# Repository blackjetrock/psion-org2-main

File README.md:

# Psion Organiser 2 Recreation Main PCB

A recreation of the Psion Organiser II main PCB using a RP Pico as the
main processor.
An OLED display replaces the original LCD, datapack gadgets supply the
non volatile storage using SD cards.
A ESP-WROOM-32 module on the board provides Wifi and maybe Bluetooth connectivity.
The module provides a hot spot that can be used to perfom actions on the Organiser
and transfer data.

The code running will hopefully be an emulation of the 6303 running one of the original
organiser ROMs with the hardware emulation done on the Pico.

Main PCB
========

This has a RP Pico on it as a controller and several IO expanders. These are because the Pico doesn't have enough GPIOs to
run all of the hardware that is needed.

Power PCB
=========

The original power PCB doesn't really fit with the new main board, so rather than try to work around it, A new PCB is used with the
new main board. It has the slot connectors and any hardware needed to drive them. The slot level shifters are on this board. It would be possible to design a different poiwer PCB that, for example, didn't have slots but had sd cards instead. The hardware for the slots is then replaced by the new PCB, but the main PCB still has whatever circuitry is needed for its own hardware.

Emulator
========

It's a bit of an odd place for it, but there is an emulator here that I used as the basis for the emulator that runs on the recreation. I did the bulk of the work on it on a PC and then moved i tto the Pico. There's now separate code for the Pico as it supports hardware on the main PCB rather than PC based keyboard and display IO. The mon-emulator is a monitored emulator that uses a second emulator to check the operation of mine so that I could find some tricky bugs. The emulator that does the monitoring is the 6303 file from Jaap's Jape emulator, ported to C.

Display
=======

The display is an OLED dot matrix graphics display. I have tried several colours, they all work, the white display is clearest I think.

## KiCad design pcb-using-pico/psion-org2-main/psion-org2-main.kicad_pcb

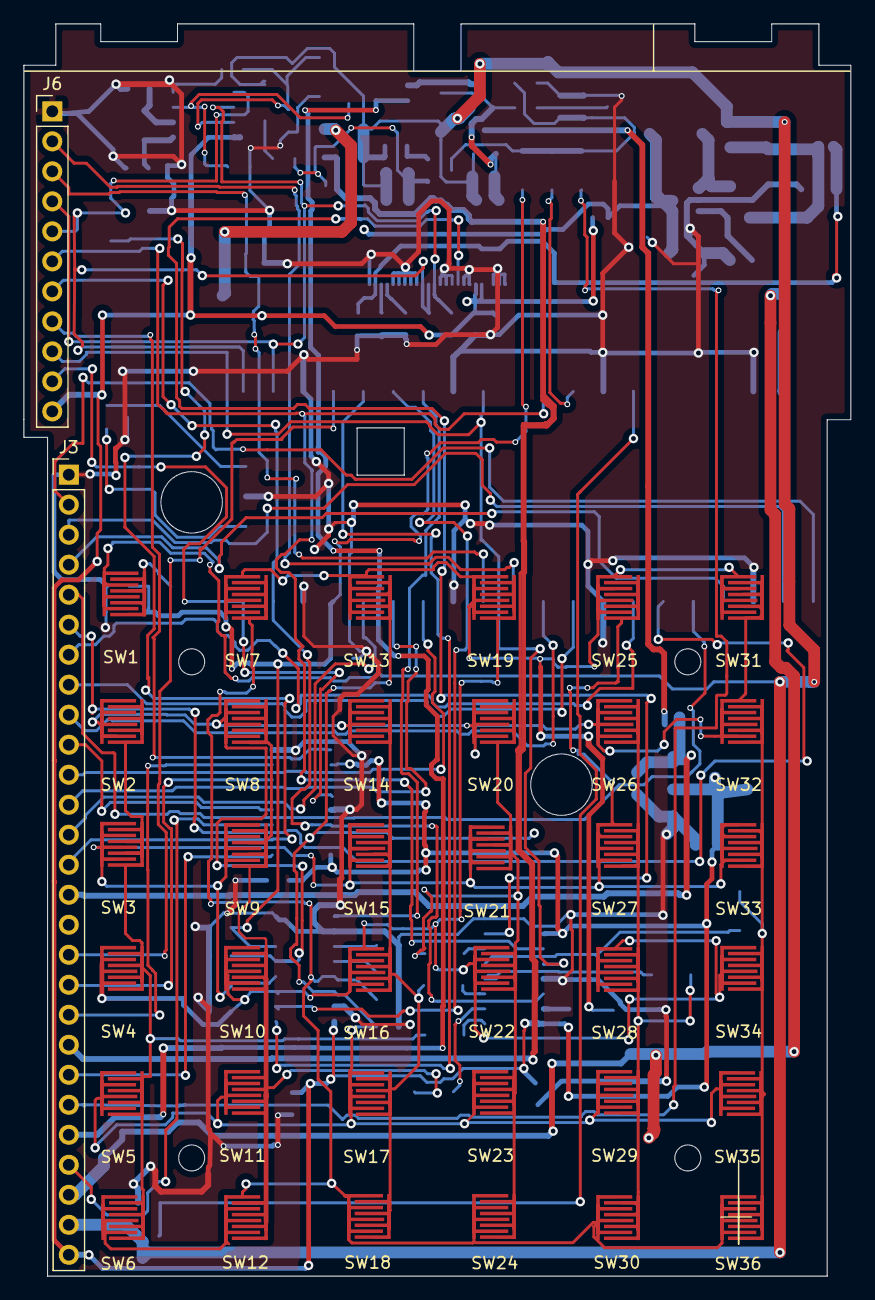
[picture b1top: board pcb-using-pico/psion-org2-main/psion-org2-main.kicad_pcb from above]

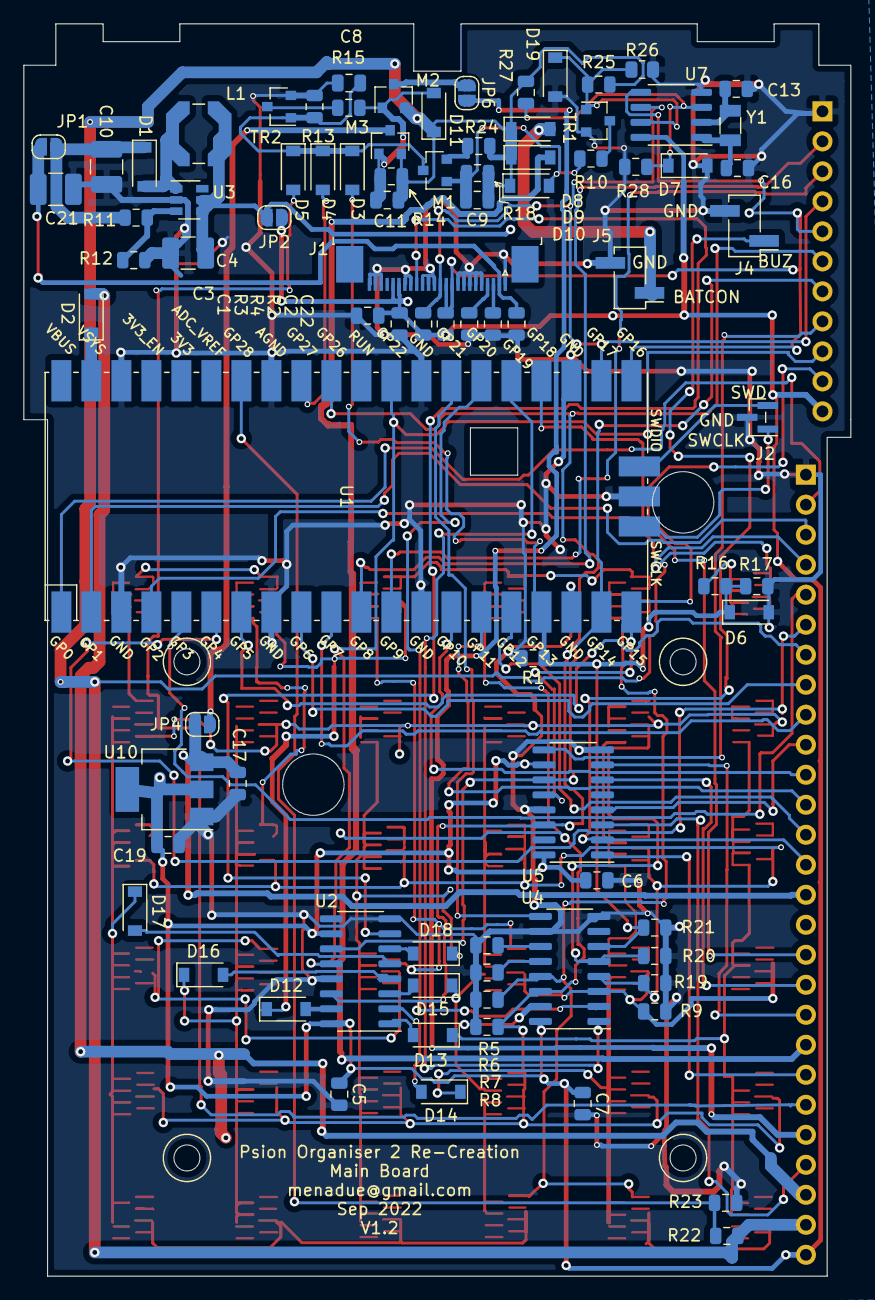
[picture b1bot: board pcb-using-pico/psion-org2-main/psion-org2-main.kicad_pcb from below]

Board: 2 copper layers, 70.0 x 106.0 mm, 124 parts (86 on the bottom side), 87 nets.

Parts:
C1: 4u7; C_0805_2012Metric
C2: 4u7 25V; C_0805_2012Metric
C3, C5, C6, C7, C8, C9, C11, C22: 100nF; C_0805_2012Metric
C4, C10: 22uF; C_1210_3225Metric_Pad1.42x2.65mm_HandSolder
C13, C16: 10pF; C_0805_2012Metric
C17, C19: 100n; C_0805_2012Metric
C21: 10uF; C_1210_3225Metric_Pad1.42x2.65mm_HandSolder
D1: SS36; D_SOD-123
D2: MBR120VLSFT1G; D_SOD-123
D3, D4, D5, D12, D13, D14, D15, D16, D17, D18: 1N4148; D_SOD-123
D6: 2v7; D_SOD-123
D7, D19: nopop; D_SOD-123
D8, D9: AECQ101; D_SOD-123
D10, D11: 4v7; D_SOD-123
J1: Conn_01x24_Female; TE_2-1734839-4_1x24-1MP_P0.5mm_Horizontal_reversed_pinout
J2: Conn_01x03_Female; PinHeader_1x03_P1.00mm_Vertical_SMD_Pin1Left
J3: Conn_01x27_Female; PinHeader_1x27_P2.54mm_Vertical
J4, J5: Conn_01x02_Female; PinHeader_1x02_P2.54mm_Vertical_SMD_Pin1Left
J6: Conn_01x11_Female; PinHeader_1x11_P2.54mm_Vertical
JP1: SolderJumper_2_Open; SolderJumper-2_P1.3mm_Open_RoundedPad1.0x1.5mm
JP2, JP4, JP6: Jumper_NO_Small; SolderJumper-2_P1.3mm_Open_RoundedPad1.0x1.5mm
L1: 22uH; L_Coilcraft_LPS5030
M1, M2, M3: Si2301; SOT-23
R1, R10, R13, R14, R15, R18, R24, R25, R26: 10k; R_0805_2012Metric
R2: 910k; R_0805_2012Metric
R3, R4: 2k; R_0805_2012Metric
R5, R6, R7, R8, R9, R19, R20, R21: 100k; R_0805_2012Metric
R11, R27: 110k; R_0805_2012Metric
R12: 5789R; R_0805_2012Metric
R16: 2k2; R_0805_2012Metric
R17: nopop; R_0805_2012Metric
R22: Not tested or calculated yet; R_0805_2012Metric
R23: Not tested of calculated yet; R_0805_2012Metric
R28: 47k; R_0805_2012Metric
SW1: AC_ON; fx502p_keypad
SW2: A; fx502p_keypad
SW3: g; fx502p_keypad
SW4: m; fx502p_keypad
SW5: s; fx502p_keypad
SW6: shft; fx502p_keypad
SW7: mode; fx502p_keypad
SW8: b; fx502p_keypad
SW9: h; fx502p_keypad
SW10: n; fx502p_keypad
SW11: t; fx502p_keypad
SW12: del; fx502p_keypad
SW13: up; fx502p_keypad
SW14: c; fx502p_keypad
SW15: i; fx502p_keypad
SW16: o; fx502p_keypad
SW17: u; fx502p_keypad
SW18: y; fx502p_keypad
SW19: down; fx502p_keypad
SW20: d; fx502p_keypad
SW21: j; fx502p_keypad
SW22: p; fx502p_keypad
SW23: v; fx502p_keypad
SW24: z; fx502p_keypad
SW25: left; fx502p_keypad
SW26: e; fx502p_keypad
SW27: k; fx502p_keypad
SW28: q; fx502p_keypad
SW29: w; fx502p_keypad
SW30: spc; fx502p_keypad
SW31: right; fx502p_keypad
SW32: f; fx502p_keypad
SW33: L; fx502p_keypad
SW34: r; fx502p_keypad
SW35: x; fx502p_keypad
SW36: exe; fx502p_keypad
TR1: Si2302CDS-n-ch; SOT-23
TR2: Si2302CDS-n-channel; SOT-23
U1: Pico; RPi_Pico_SMD
U2, U5: 74HC595; SOIC-16_3.9x9.9mm_P1.27mm
U3: Regulator_Switching_MT3608; SOT-23-6
U4: 74LS165; SOIC-16_3.9x9.9mm_P1.27mm
U7: MCP7940N-xSN; SO-8_3.9x4.9mm_P1.27mm
U10: AMS1117-3.3; SOT-223-3_TabPin2
Y1: 32k768Hz; Crystal_SMD_3215-2Pin_3.2x1.5mm

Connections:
5V: D2.2, J3.25
5V_ON: J3.24, U5.3
+3V3: C1.1, C3.1, C5.1, C6.1, C7.1, C19.1, J1.5, J1.6, J3.27, J6.11, JP2.1, R3.1, R4.1, U2.10, U2.16, U4.16, U5.10, U5.16, U7.8, U10.2
BATCON: D8.2, J5.1
BUZZER: J3.14, J4.1, U5.2
ESP_ON: J3.21, U5.1
EXT_PWR_IN: D9.2, J3.20
EX_ON: D5.2, J3.22
GND: C1.2, C2.2, C3.2, C4.2, C5.2, C6.2, C7.2, C8.2, C10.2, C13.2, C16.2, C17.2, C19.2, C21.2, C22.2, D6.2, D7.2, D19.2, J1.1, J1.2, J1.3, J1.7, J1.8, J1.10, J1.11, J1.12, J1.16, J1.17, J1.18, J1.19, J1.20, J1.24, J2.2, J3.1, J4.2, J5.2, J6.1, R1.2, R2.2, R5.2, R6.2, R7.2, R8.2, R9.2, R12.2, R13.2, R17.2, R19.2, R20.2, R21.2, R23.2, R26.2, R28.2, TR1.2, TR2.2, U1.3, U1.8, U1.13, U1.18, U1.23, U1.28, U1.33, U1.38, U1.42, U2.8, U2.13, U3.2, U4.8, U4.10, U4.15, U5.8, U5.13, U7.4, U10.1
K1: D12.1, SW7.1, SW13.1, SW19.1, SW25.1, SW31.1
K2: D13.1, SW2.2, SW3.2, SW4.2, SW5.2, SW6.2
K3: D14.1, SW8.2, SW9.2, SW10.2, SW11.2, SW12.2
K4: D15.1, SW14.2, SW15.2, SW16.2, SW17.2, SW18.2
K5: D16.1, SW26.2, SW27.2, SW28.2, SW29.2, SW30.2
K6: D17.1, SW32.2, SW33.2, SW34.2, SW35.2, SW36.2
K7: D18.1, SW20.2, SW21.2, SW22.2, SW23.2, SW24.2
LATCHIN: U1.25, U4.1
LATCHOUT1: J6.9, U1.29, U2.12
LATCHOUT2: J6.10, U1.20, U5.12
LS_DIR: J3.17, U1.24
unnamed: C2.1, J1.22
unnamed: C4.1, JP2.2, L1.1, U3.4, U3.5
unnamed: C8.1, D3.1, D4.1, D5.1, M1.3, R13.1, TR2.1
unnamed: C9.2, D10.2, M1.1, R10.2, R18.2
unnamed: C10.1, D1.1, JP1.1, R11.1
unnamed: C11.2, D11.2, M2.1, M3.1, R14.2, R15.1
unnamed: C13.1, U7.2, Y1.2
unnamed: C16.1, U7.1, Y1.1
unnamed: D1.2, L1.2, U3.1
unnamed: D2.1, U1.39
unnamed: D7.1, R27.2, R28.1, U7.3
unnamed: D12.2, U2.15
unnamed: D13.2, U2.1
unnamed: D14.2, U2.2
unnamed: D15.2, U2.3
unnamed: D16.2, U2.4
unnamed: D17.2, U2.5
unnamed: D18.2, U2.6
unnamed: J1.21, R2.1
unnamed: JP4.1, M3.3
unnamed: JP6.1, M2.3
unnamed: M1.2, R24.2
unnamed: R10.1, TR1.3
unnamed: R11.2, R12.1, U3.3
unnamed: R15.2, TR2.3
unnamed: R16.1, SW1.2
unnamed: R22.2, R23.1, U1.34
OLED_RES: J1.9, U2.7
OLED_SCL: J1.13, J6.4, R3.2, U1.22, U7.6
OLED_SDA: J1.14, J1.15, J6.5, R4.2, U1.21, U7.5
P50: R5.1, U4.11
P51: R6.1, U4.12
P52: R7.1, SW6.1, SW7.2, SW12.1, SW18.1, SW24.1, SW30.1, SW36.1, U4.13
P53: R8.1, SW5.1, SW11.1, SW13.2, SW17.1, SW23.1, SW29.1, SW35.1, U4.14
P54: R9.1, SW4.1, SW10.1, SW16.1, SW19.2, SW22.1, SW28.1, SW34.1, U4.3
P55: R19.1, SW3.1, SW9.1, SW15.1, SW21.1, SW25.2, SW27.1, SW33.1, U4.4
P56: R20.1, SW2.1, SW8.1, SW14.1, SW20.1, SW26.1, SW31.2, SW32.1, U4.5
P57: D3.2, D6.1, R1.1, R16.2, R17.1, R21.1, U1.17, U4.6
PICO_RX: J6.3, U1.12
PICO_TX: J6.2, U1.11
QH_O: J6.8, U5.9
RTC_MFP: D19.1, R25.2, R26.1, TR1.1, U7.7
SCLK: J3.11, U1.14
SCLKIN: U1.26, U4.2
SCLKOUT: J6.6, U1.31, U2.11, U5.11
SC_OE: J3.19, U5.7
SD0: J3.2, U1.1
SD1: J3.3, U1.2
SD2: J3.4, U1.4
SD3: J3.5, U1.5
SD4: J3.6, U1.6
SD5: J3.7, U1.7
SD6: J3.8, U1.9
SD7: J3.9, U1.10
SDAIN: U1.27, U4.9
SDAOUT: J6.7, U1.19, U2.14, U5.14
SD_OE: J3.18, U5.6
SMR: J3.13, U1.16
SOE: J3.12, U1.15
SPGM: J3.10, U5.4
SWCLK: J2.1, U1.41
SWD: J2.3, U1.43
VBAT: C9.1, C11.1, D8.1, D9.1, D10.1, D11.1, J3.26, M2.2, M3.2, R14.1, R18.1, R22.1, R24.1, R25.1, R27.1, SW1.1
VBAT_SWITCHED1: C17.1, J3.15, JP4.2, U10.3
VBAT_SWITCHED2: J3.23, JP6.2
VBAT_SW_ON: D4.2, U1.32
VOLED: C21.1, C22.1, J1.23, JP1.2

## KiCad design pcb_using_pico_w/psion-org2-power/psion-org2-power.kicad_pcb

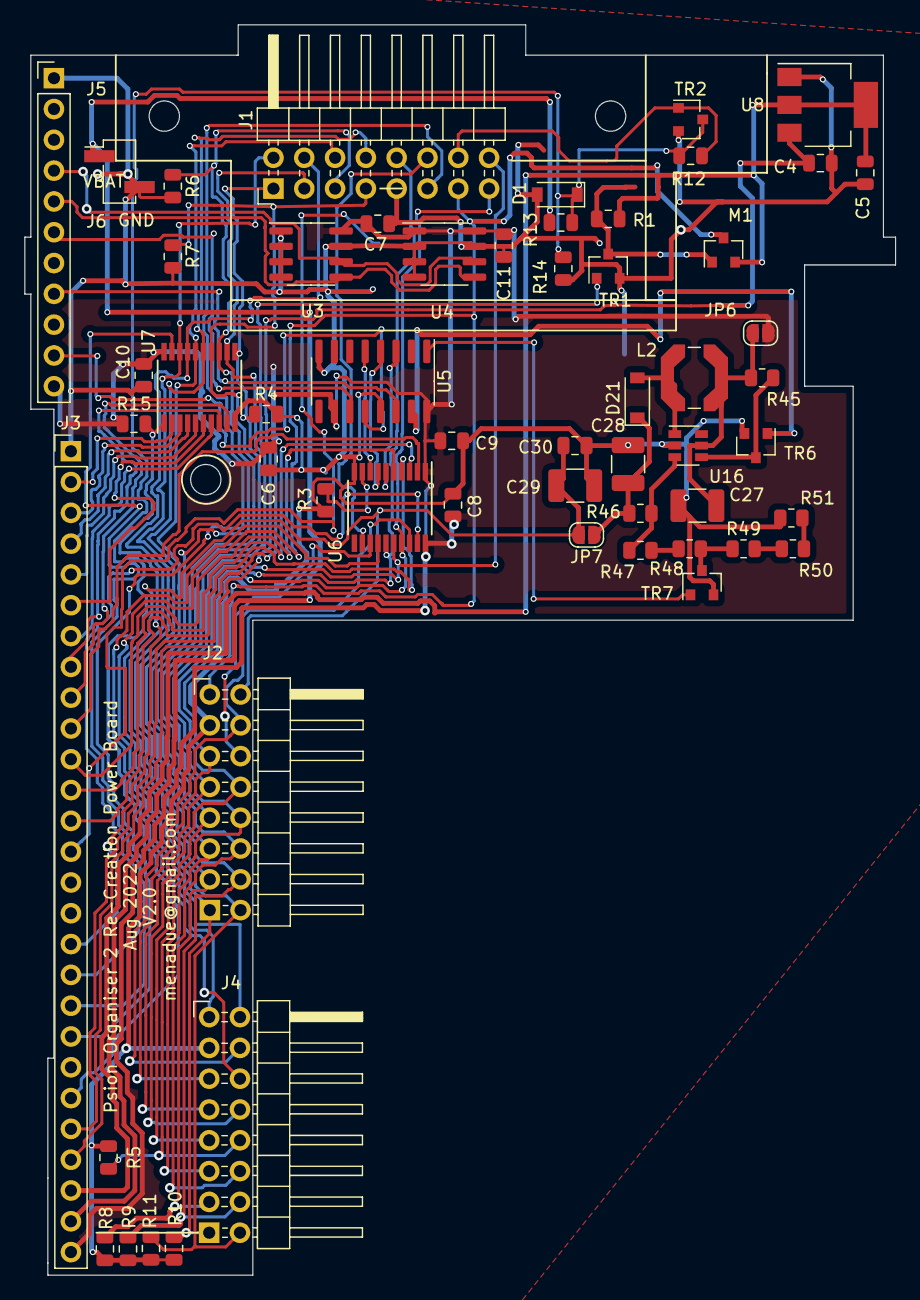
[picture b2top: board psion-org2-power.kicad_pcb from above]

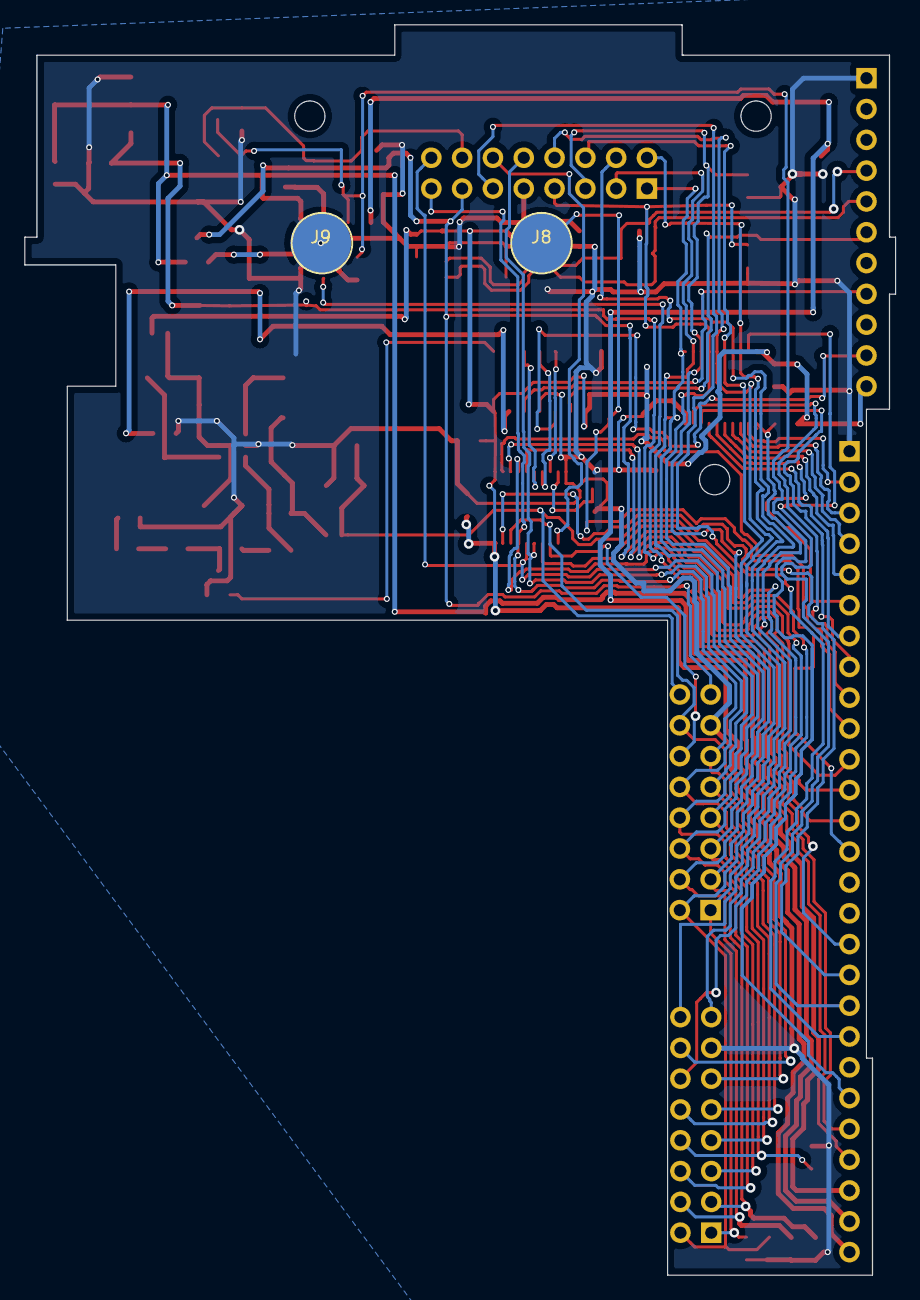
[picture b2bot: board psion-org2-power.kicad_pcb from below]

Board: 2 copper layers, 71.8 x 103.1 mm, 58 parts (2 on the bottom side), 63 nets.

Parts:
C4, C5, C30: 100nF; C_0805_2012Metric
C6, C7, C8, C9, C10, C11: 100n; C_0805_2012Metric
C27, C28: 22uF; C_1210_3225Metric_Pad1.33x2.70mm_HandSolder
C29: 10uF; C_1210_3225Metric_Pad1.33x2.70mm_HandSolder
D1: 3V0; D_SOD-123
D21: SS36; D_SOD-123
J1: Conn_02x08_Odd_Even; PinHeader_2x08_P2.54mm_Horizontal
J2, J4: Conn_02x08_Odd_Even; PinHeader_2x08_P2.54mm_Horizontal_psionSide
J3: Conn_01x27_Female; PinHeader_1x27_P2.54mm_Vertical
J5: Conn_01x11_Female; PinHeader_1x11_P2.54mm_Vertical
J6: Conn_01x02_Female; PinHeader_1x02_P2.54mm_Vertical_SMD_Pin1Left
J8, J9: Conn_01x01_Female; psion_beeper_pad
JP6: Jumper_NO_Small; SolderJumper-2_P1.3mm_Open_RoundedPad1.0x1.5mm
JP7: SolderJumper_2_Open; SolderJumper-2_P1.3mm_Open_RoundedPad1.0x1.5mm
L2: 22uH; L_Coilcraft_LPS5030
M1: P-CHANNEL-MOSFET; SOT-23
R1, R13, R14, R45: 10k; R_0805_2012Metric
R3, R4, R5, R6, R7, R8, R9, R10, R11, R12, R15: 100k; R_0805_2012Metric
R46: 180k; R_0805_2012Metric
R47: 5k1; R_0805_2012Metric
R48, R51: 100R; R_0805_2012Metric
R49: 18k; R_0805_2012Metric
R50: 1k2; R_0805_2012Metric
TR1: Si2302CDS-n-channel; SOT-23
TR2, TR6, TR7: Si2302CDS-n-ch; SOT-23
U3, U4: CAT24C256; SOIC-8_3.9x4.9mm_P1.27mm
U5: 74HC595; SOIC-16_3.9x9.9mm_P1.27mm
U6, U7: 74LS245; TSSOP-20_4.4x6.5mm_P0.65mm
U8: AMS1117-5.0; SOT-223-3_TabPin2
U16: Regulator_Switching_MT3608; SOT-23-6

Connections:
5V: C5.1, J3.25, M1.2, R1.1, U8.2
5V_ON: J3.24, TR1.1
+3V3: C6.1, C7.1, C8.1, C9.1, C10.1, C11.1, J3.27, J5.11, JP6.1, R15.1, U3.8, U4.1, U4.8, U5.10, U5.16, U6.1, U6.20, U7.20
BUZZER: J3.14, J8.1
EXT_PWR_IN: J1.11, J3.20
EX_ON: J1.14, R12.2, TR2.1
EX_ON_INV: D1.1, J3.22, R12.1, R13.2, R14.1, TR2.3
GND: C4.2, C5.2, C6.2, C7.2, C8.2, C9.2, C10.2, C11.2, C27.2, C28.2, C29.2, C30.2, D1.2, J1.9, J2.13, J3.1, J4.13, J5.1, J6.2, J9.1, R3.2, R4.2, R5.2, R6.2, R7.2, R8.2, R9.2, R10.2, R11.2, R14.2, R51.2, TR1.2, TR2.2, TR6.2, TR7.2, U3.1, U3.2, U3.3, U3.4, U3.7, U4.2, U4.3, U4.4, U4.7, U5.8, U5.13, U6.10, U7.10, U8.1, U16.2
LATCHOUT2: J5.10, U5.12
LS_DIR: J3.17, R15.2, U7.1
unnamed: C27.1, JP6.2, L2.1, R45.1, U16.5
unnamed: C28.1, D21.1, JP7.1, R46.1
unnamed: D21.2, L2.2, U16.1
unnamed: M1.1, R1.2, TR1.3
unnamed: R3.1, U6.9
unnamed: R45.2, TR6.3, U16.4
unnamed: R46.2, R47.1, U16.3
unnamed: R47.2, R48.1
unnamed: R48.2, R49.1, TR7.3
unnamed: R49.2, R50.1
unnamed: R50.2, R51.1
OLED_SCL: J5.4, U3.6, U4.6
OLED_SDA: J5.5, U3.5, U4.5
P_SCLK: J1.10, J2.10, J4.10, U6.15
P_SD0: J1.2, J2.2, J4.2, R11.1, U7.18
P_SD1: J1.4, J2.1, J4.1, R10.1, U7.17
P_SD2: J1.6, J2.4, J4.4, R9.1, U7.16
P_SD3: J1.8, J2.3, J4.3, R8.1, U7.15
P_SD4: J1.7, J2.6, J4.6, R7.1, U7.14
P_SD5: J1.5, J2.5, J4.5, R6.1, U7.13
P_SD6: J1.3, J2.8, J4.8, R5.1, U7.12
P_SD7: J1.1, J2.7, J4.7, R4.1, U7.11
P_SMR: J1.16, J2.9, J4.9, U6.16
P_SOE: J1.15, J2.11, J4.11, U6.17
P_SPGM: J2.14, J4.14, U6.18
P_SS1: J4.12, U6.14
P_SS2: J2.12, U6.13
P_SS3: J1.12, U6.12
QH_O: J5.8, U5.14
SCLK: J3.11, U6.5
SCLKOUT: J5.6, U5.11
SC_OE: J3.19, U7.19
SD0: J3.2, U7.2
SD1: J3.3, U7.3
SD2: J3.4, U7.4
SD3: J3.5, U7.5
SD4: J3.6, U7.6
SD5: J3.7, U7.7
SD6: J3.8, U7.8
SD7: J3.9, U7.9
SD_OE: J3.18, U6.19
SMR: J3.13, U6.4
SOE: J3.12, U6.3
SPGM: J3.10, U6.2
SS1: U5.3, U6.6
SS2: U5.4, U6.7
SS3: U5.5, U6.8
VBAT: J3.26, J6.1, R13.1
VBAT_SWITCHED2: C4.1, J3.23, U8.3
VCC_SLOT: J1.13, J2.15, J4.15, M1.3
VPP_DRIVE: C29.1, C30.1, J2.16, J4.16, JP7.2
VPP_ON: TR6.1, U5.15
VPP_VOLT_SELECT: TR7.1, U5.1

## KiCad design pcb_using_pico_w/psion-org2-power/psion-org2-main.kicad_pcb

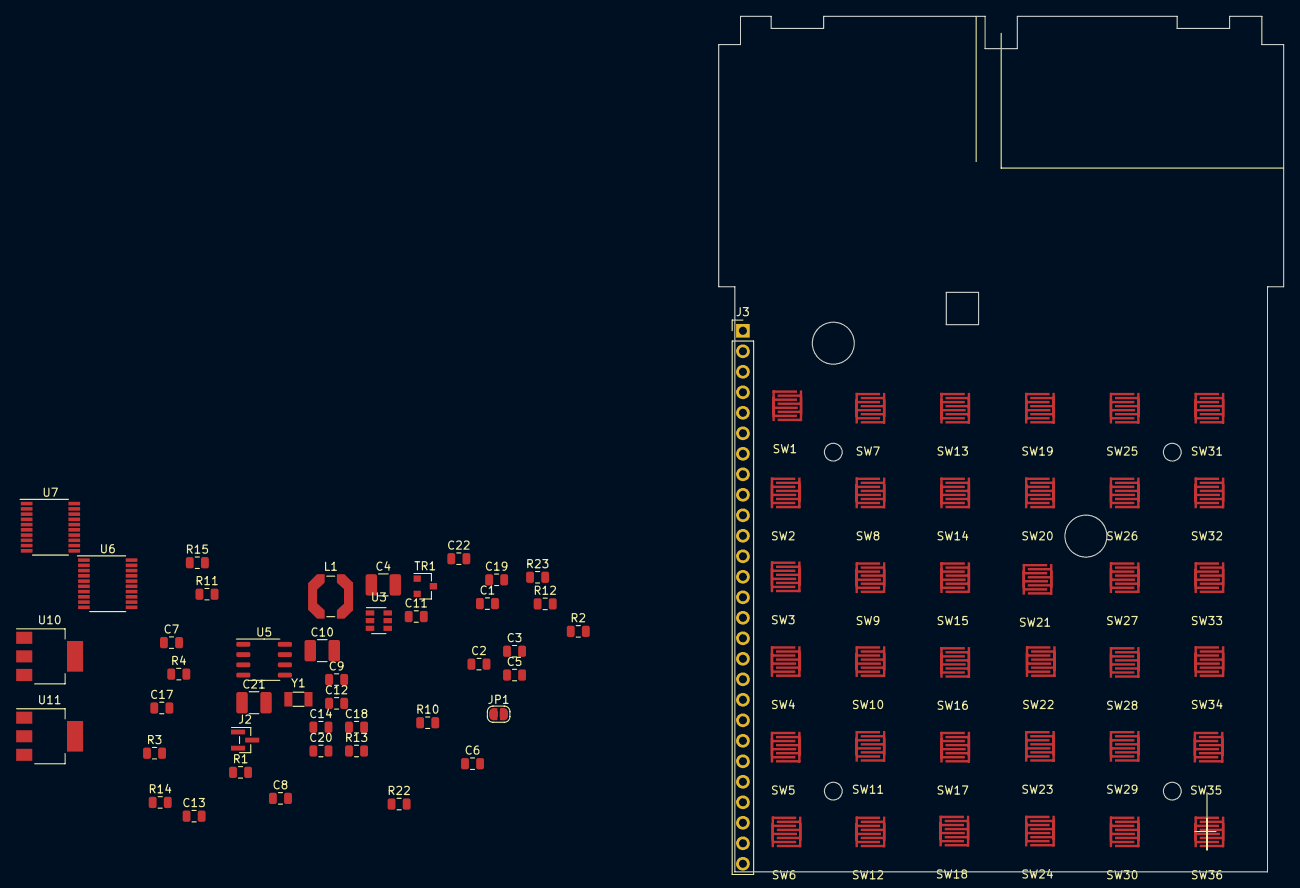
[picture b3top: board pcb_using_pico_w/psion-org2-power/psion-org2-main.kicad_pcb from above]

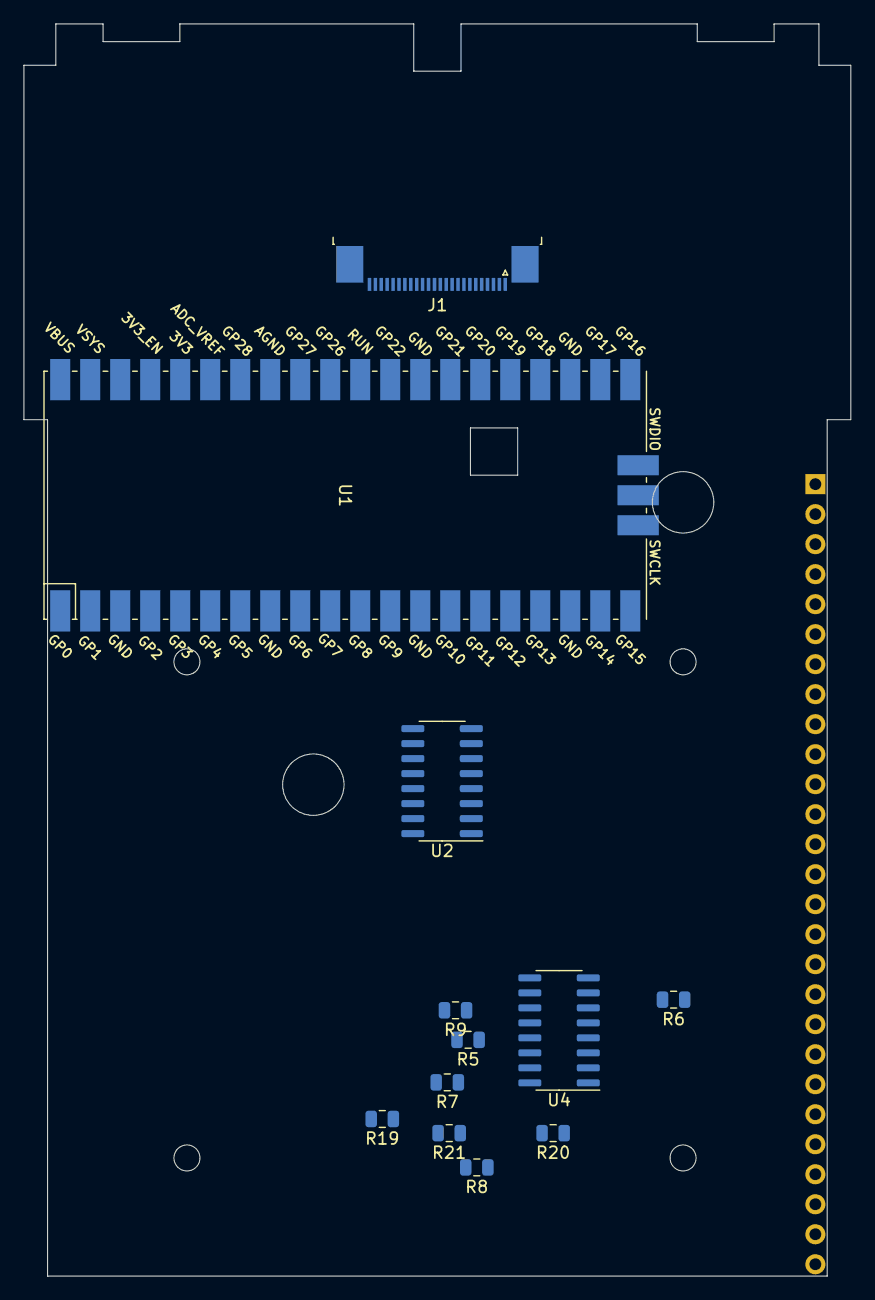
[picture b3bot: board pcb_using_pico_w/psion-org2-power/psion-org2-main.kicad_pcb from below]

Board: 2 copper layers, 70.0 x 106.0 mm, 92 parts (12 on the bottom side), 73 nets, no tracks yet.

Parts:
C1: 4u7; C_0805_2012Metric
C2: 4u7 25V; C_0805_2012Metric
C3, C22: 100nF; C_0805_2012Metric
C4, C10: 22uF; C_1210_3225Metric_Pad1.42x2.65mm_HandSolder
C5: 1u; C_0805_2012Metric
C6, C7, C8, C9, C11, C12: 100n; C_0805_2012Metric
C13, C14: C; C_0805_2012Metric
C17, C18, C19, C20: C_Small; C_0805_2012Metric
C21: 10uF; C_1210_3225Metric_Pad1.42x2.65mm_HandSolder
J1: Conn_01x24_Female; TE_2-1734839-4_1x24-1MP_P0.5mm_Horizontal_reversed_pinout
J2: Conn_01x03_Female; PinHeader_1x03_P1.00mm_Vertical_SMD_Pin1Left
J3: Conn_01x27_Female; PinHeader_1x27_P2.54mm_Vertical
JP1: SolderJumper_2_Open; SolderJumper-2_P1.3mm_Open_RoundedPad1.0x1.5mm
L1: 22uH; L_Coilcraft_LPS5030
R1, R3, R4: 10k; R_0805_2012Metric
R2: 910k; R_0805_2012Metric
R5, R6, R7, R8, R9, R19, R20, R21: 100k; R_0805_2012Metric
R10: 49R; R_0805_2012Metric
R11: 120k; R_0805_2012Metric
R12: 18k; R_0805_2012Metric
R13, R14: 4k7; R_0805_2012Metric
R15, R22, R23: R_Small; R_0805_2012Metric
SW1: AC_ON; fx502p_keypad
SW2: A; fx502p_keypad
SW3: g; fx502p_keypad
SW4: m; fx502p_keypad
SW5: s; fx502p_keypad
SW6: shft; fx502p_keypad
SW7: mode; fx502p_keypad
SW8: b; fx502p_keypad
SW9: h; fx502p_keypad
SW10: n; fx502p_keypad
SW11: t; fx502p_keypad
SW12: del; fx502p_keypad
SW13: up; fx502p_keypad
SW14: c; fx502p_keypad
SW15: i; fx502p_keypad
SW16: o; fx502p_keypad
SW17: u; fx502p_keypad
SW18: y; fx502p_keypad
SW19: down; fx502p_keypad
SW20: d; fx502p_keypad
SW21: j; fx502p_keypad
SW22: p; fx502p_keypad
SW23: v; fx502p_keypad
SW24: z; fx502p_keypad
SW25: left; fx502p_keypad
SW26: e; fx502p_keypad
SW27: k; fx502p_keypad
SW28: q; fx502p_keypad
SW29: w; fx502p_keypad
SW30: spc; fx502p_keypad
SW31: right; fx502p_keypad
SW32: f; fx502p_keypad
SW33: L; fx502p_keypad
SW34: r; fx502p_keypad
SW35: x; fx502p_keypad
SW36: exe; fx502p_keypad
TR1: Si2302CDS-n-channel; SOT-23
U1: Pico; RPi_Pico_SMD
U2: 74HC595; SOIC-16_3.9x9.9mm_P1.27mm
U3: Regulator_Switching_MT3608; SOT-23-6
U4: 74LS165; SOIC-16_3.9x9.9mm_P1.27mm
U5: MCP7940N-xSN; SO-8_3.9x4.9mm_P1.27mm
U6, U7: 74LS245; TSSOP-20_4.4x6.5mm_P0.65mm
U10, U11: AMS1117-3.3; SOT-223-3_TabPin2
Y1: 32k768Hz; Crystal_SMD_3215-2Pin_3.2x1.5mm

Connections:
+3V3: C1.1, C3.1, C4.1, C5.1, C6.1, C7.1, C8.1, C9.1, C11.1, C12.1, J1.5, J1.6, J3.27, L1.1, R3.1, R4.1, R13.1, R14.1, R15.1, SW1.1, U2.10, U2.16, U3.4, U3.5, U4.16, U5.8, U6.1, U6.20, U7.20
DRV_HV: TR1.1, U1.34
GND: C1.2, C2.2, C3.2, C5.2, C6.2, C7.2, C8.2, C9.2, C11.2, C12.2, C13.2, C14.2, C17.2, C18.2, C19.2, C20.2, J1.1, J1.2, J1.3, J1.7, J1.8, J1.11, J1.12, J1.16, J1.17, J1.18, J1.19, J1.20, J1.24, J2.2, J3.1, R1.2, R2.2, R5.2, R6.2, R7.2, R8.2, R9.2, R19.2, R20.2, R21.2, R23.2, TR1.2, U1.3, U1.8, U1.13, U1.18, U1.23, U1.28, U1.33, U1.42, U2.8, U2.13, U4.8, U4.10, U4.15, U5.4, U6.10, U6.19, U7.10, U7.19, U10.1, U11.1
K1: SW7.1, SW13.1, SW19.1, SW25.1, SW31.1, U2.15
K2: SW2.2, SW3.2, SW4.2, SW5.2, SW6.2, U2.1
K3: SW7.2, SW8.2, SW9.2, SW10.2, SW11.2, SW12.2, U2.2
K4: SW13.2, SW14.2, SW15.2, SW16.2, SW17.2, SW18.2, U2.3
K5: SW25.2, SW26.2, SW27.2, SW28.2, SW29.2, SW30.2, U2.4
K6: SW31.2, SW32.2, SW33.2, SW34.2, SW35.2, SW36.2, U2.5
K7: SW19.2, SW20.2, SW21.2, SW22.2, SW23.2, SW24.2, U2.6
LATCHIN: U1.25, U4.1
LATCHOUT: U1.29, U2.12
LS_DIR: R15.2, U7.1
unnamed: C2.1, J1.22
unnamed: C10.1, JP1.1, R11.1
unnamed: C4.2, C10.2, C21.2, C22.2, R10.2, R12.2, U3.2
unnamed: C13.1, U5.2, Y1.2
unnamed: C14.1, U5.1, Y1.1
unnamed: L1.2, U3.1
unnamed: J1.21, R2.1
unnamed: R10.1, TR1.3
unnamed: R11.2, R12.1, U3.3
unnamed: R22.2, R23.1, U5.3
OLED_RES: J1.9, U2.7
OLED_SCL: J1.13, R3.2, U1.22
OLED_SDA: J1.14, J1.15, R4.2, U1.21
P50: R5.1, U4.11
P51: R6.1, U4.12
P52: R7.1, SW6.1, SW12.1, SW18.1, SW24.1, SW30.1, SW36.1, U4.13
P53: R8.1, U4.14
P54: R9.1, SW4.1, SW10.1, SW16.1, SW22.1, SW28.1, SW34.1, U4.3
P55: R19.1, SW3.1, SW9.1, SW15.1, SW21.1, SW27.1, SW33.1, U4.4
P56: R20.1, SW2.1, SW8.1, SW14.1, SW20.1, SW26.1, SW32.1, U4.5
P57: R1.1, R21.1, SW1.2, U1.17, U4.6
P_SCLK: U1.14, U6.14
P_SD0: U1.1, U7.18
P_SD1: U1.2, U7.17
P_SD2: U1.4, U7.16
P_SD3: U1.5, U7.15
P_SD4: U1.6, U7.14
P_SD5: U1.7, U7.13
P_SD6: U1.9, U7.12
P_SD7: U1.10, U7.11
P_SMR: U1.16, U6.15
P_SOE: U1.15, U6.16
P_SPGM: U1.11, U6.18
P_SS: U1.12, U6.17
RTC_SCL: R14.2, U5.6
RTC_SDA: R13.2, U5.5
SCLK: J3.12, U6.6
SCLKIN: U1.26, U4.2
SCLKOUT: U1.31, U2.11
SD0: J3.2, U7.2
SD1: J3.3, U7.3
SD2: J3.4, U7.4
SD3: J3.5, U7.5
SD4: J3.6, U7.6
SD5: J3.7, U7.7
SD6: J3.8, U7.8
SD7: J3.9, U7.9
SDAIN: U1.27, U4.9
SDAOUT: U1.32, U2.14
SMR: J3.14, U6.5
SOE: J3.13, U6.4
SPGM: J3.10, U6.2
SS: J3.11, U6.3
SWCLK: J2.1, U1.41
SWD: J2.3, U1.43
VBAT: C17.1, C18.1, J3.26, R22.1, U10.3, U11.3
VOLED: C21.1, C22.1, J1.23, JP1.2
VccESP: C20.1, U11.2
VccPico: C19.1, U10.2
p53: SW5.1, SW11.1, SW17.1, SW23.1, SW29.1, SW35.1

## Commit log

2021-09-14 Initial checkin
2021-09-14 Updates to control PCB schematic
2021-09-14 More updates
2021-09-16 Schematic updates
2021-10-17 Added start of code for main board replacement. Wifi server
2021-10-18 Added emulator directory
2021-10-18 Emulator updates
2021-10-19 Updates to emulator
2021-10-19 Added git ignore file
2021-10-19 Added better 6303 datasheet
2021-10-20 More instructions emulated
2021-10-23 Updates, runs further now after fixes
2021-10-24 More instructions added, bugs fixed
2021-10-24 Runs forever. No hardware emulation
2021-10-24 Interrupts
2021-10-24 Runs. LCD controller needs work
2021-10-25 More updates and fixes
2021-10-26 Emulator runs copyright message and FIND
2021-10-27 Added memory reference code
2021-10-29 Runs to main menu
2021-10-29 more fixes
2021-10-29 More instructions
2021-10-29 Updates to status displays
2021-10-29 Fixed V flag in ASL
2021-10-30 kb working better now
2021-10-30 Updated RAM dump to add ascii
2021-11-01 Works with V3.3 XA ROM
2021-11-02 PCB updates
2021-11-02 Tidy up
2021-11-07 Last commit before splitting to two PCBs
2021-11-07 Archive before split added
2021-11-08 Created power PCB
2021-11-08 Updates to power PCB
2021-11-09 Updates to both PCBs
2021-11-11 Added second connector, eeprom on power pcb
2021-11-12 Start of PCB layout
2021-11-12 First main PCB layout
2021-11-13 First layouts for fabrication
2021-11-13 Small updates and sent to fab
2021-12-05 Added fab1 archive and small fixes to emulator
2021-12-06 Runs OPL
2021-12-07 Added bank switching for LZ
2021-12-07 Updated .gitignore
2021-12-08 Updates after fab1
2021-12-25 Annotated ROM listin gupdate
2021-12-25 Annotated ROM listing update
2021-12-27 V1.1 started
2021-12-28 V1.1 PCBs
2021-12-28 fab2 V1.1
2021-12-28 V1_1 sent to fab
2022-07-25 Updated missing values on schematics, pushed those through to the PCB and created BOM .csv files for those schematics. Created .pdf files for schematics to mitigate the missing library problem of Kic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
2022-08-20 Added power board with VPP 21V supply
2022-08-21 Fixed comment typo. Reverted schematic to previous version (966dcfb2f9e5fb2f0f6e9c85d958500d25748731) as a change (7bf7705c572b4e37423d66cfa6dac4b195edf464) somehow managed to create a bad hierarchic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
